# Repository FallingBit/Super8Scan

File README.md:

# Super8Scan

Progetto completo di uno **scanner per pellicole Super8 e Normal8** fatto in casa, a cura di **FallingBit**:
hardware, firmware e software.

Un proiettore modificato fa avanzare la pellicola un fotogramma alla volta; quando l'immagine è ferma simula il click
di un mouse. Un programma per Windows salva a ogni click il fotogramma ripreso da una scheda di acquisizione HDMI/USB
in 4K, controlla la qualità dei fotogrammi e alla fine crea il video MP4.

## Il sistema

Un proiettore Super8/Normal8 **Silma Bivox "D" Lux** modificato è comandato da un **ESP32**. La lampada è sostituita
da un pannello LED a 4000 K e la camera (scheda di acquisizione HDMI/USB 4K) riprende direttamente nell'obiettivo,
senza telo, con tutto il fotogramma e il foro della pellicola. Il cuore del sistema:

- **Motore passo-passo** NEMA 17 con driver TMC2208, collegato alla meccanica originale del proiettore;
- **Sensore Hall** e un magnete sulla ruota dello shutter, per sapere quando il fotogramma è fermo;
- **Optoisolatore** (PC817) collegato al tasto sinistro di un mouse USB: l'ESP32 "fa click" al momento giusto;
- **Display OLED** e led del pannello originale per le informazioni;
- alimentazione a **24 V** (motore), 12 V (illuminazione) e 5 V (logica).

### Funzioni della manopola

Con la manopola originale del proiettore si scelgono le funzioni:

| Posizione della manopola | Funzione |
|---|---|
| **Centro (riposo)** | **STOP**: tutto fermo, lampada spenta |
| Centro, **manopola premuta** | **Caricamento della pellicola**: il motore gira finché la tieni premuta e fa avanzare la pellicola nella meccanica, senza lampada e senza click |
| **1 scatto a destra** | **Lampada accesa**, motore fermo: serve a posizionare la camera davanti all'obiettivo, inquadrare e mettere a fuoco |
| **2 scatti a destra** | **Scansione**: il motore gira, un sensore Hall rileva il fotogramma fermo e l'ESP32 simula il click di un mouse; Super8Scan salva il fotogramma a ogni click |
| **1 scatto a sinistra** | Lampada accesa, motore fermo (preparazione alla marcia indietro) |
| **2 scatti a sinistra** | **Marcia indietro**: il motore gira al contrario, a metà velocità, con la lampada accesa. Serve a tornare indietro di **qualche fotogramma**, per esempio per ripetere la scansione di un tratto |
| **3 scatti a sinistra** | STOP (lampada spenta) |

Non c'è il riavvolgimento veloce: per riavvolgere la bobina si completa la scansione, si fa uscire tutta la pellicola
dal proiettore e la si riavvolge a parte.

Fermando il proiettore si ferma anche l'acquisizione, che può essere ripresa dallo stesso punto anche il giorno dopo.
Prima di cominciare, il puntatore del mouse va posizionato sulla finestra di Super8Scan.

## Esempi di fotogrammi

Quattro fotogrammi di esempio, salvati direttamente dal programma alla massima qualità (4K, JPEG qualità 100), senza
alcuna elaborazione e senza metadati. Cliccando sulla miniatura si apre l'originale (circa 8-9 MB). Si vede l'intero gate,
compreso il foro della pellicola usato dal controllo dei fotogrammi; le immagini sono come le riprende la telecamera
(capovolte: nel video il programma le ribalta con l'opzione apposita).

| | |
|---|---|
|  |  |
|  |  |

**Video di esempio** (Super8, creato da una scansione fatta con questo scanner): <https://youtu.be/SkZqkTiNc5s>

## Contenuto del repository

| Cartella | Contenuto | Stato |
|---|---|---|
| [`software/`](software) | **Super8Scan** per Windows (Python): acquisizione a ogni click, controllo dei fotogrammi, creazione MP4, log delle lavorazioni ([cronologia](software/CHANGELOG.md)) | 1.1.3 |
| [`firmware/`](firmware) | Firmware Arduino per l'ESP32: manopola, motore, lampada, click, display | v2.27 |
| [`hardware/`](hardware) | Descrizione del proiettore modificato, componenti, alimentazione, schema a blocchi; progetto KiCad, gerber del **PCB rev. 2.1** | rev. 2.1 |
| [`docs/`](docs) | Foto del prototipo, immagine del PCB e [fotogrammi di esempio](docs/esempi) | |

## Cosa serve

- **Un proiettore** Super8 (o Normal8) da modificare. Quello usato è un Silma Bivox "D" Lux, ma ogni proiettore con
  meccanica a griffa e shutter a ruota si può adattare. Vedi [`hardware/`](hardware) per l'elenco dei componenti e le
  modifiche.
- **Una scheda di acquisizione** USB con ingresso HDMI (4K UHD) e una camera con uscita HDMI.
- **Un PC con Windows** e Python per il software (vedi sotto).
- Per il firmware: Arduino IDE, una scheda ESP32 (WROOM-32) e le librerie indicate in [`firmware/`](firmware).

## Software Super8Scan

1. Collega la scheda di acquisizione e premi **Apri telecamera** (4K UHD, MJPG o YUY2).
2. Scegli cartella e nome del film, formato (JPG qualità 85–100, oppure PNG senza perdita) e l'attesa dopo il click.
3. **Avvia acquisizione**: ogni click sinistro del mouse, in qualsiasi punto dello schermo, salva un fotogramma
   (`fotogramma_000001.jpg`, ...). Il pulsante *Ferma* non conta. Se la cartella contiene già fotogrammi, la
   numerazione prosegue.
   **Avviso di giuntura**: una bobina da 15 m ha circa 3600 fotogrammi e le bobine più grandi sono bobine piccole
   giuntate dopo lo sviluppo. Intorno a 3600, 7200, 10800… (da 200 fotogrammi prima a 200 dopo, regolabile) la cornice
   dell'anteprima diventa **gialla**, compare un avviso e, se vuoi, suona un segnale: le vecchie giunture possono
   staccarsi o fare uno sbalzo nella meccanica. Le impostazioni sono sotto il pulsante *Avvia acquisizione*; il conteggio
   usa il numero del fotogramma, quindi vale anche se la scansione riprende in una cartella già avviata.
4. **Controllo dei fotogrammi**: il programma misura la posizione del **foro** della pellicola (a sinistra) in tutti i
   fotogrammi. Se è spostato, deformato o sfocato (scia), il fotogramma è sospetto: li vedi in un elenco con le
   miniature e decidi tu quali scartare. Gli scartati non si cancellano: nel video si possono saltare oppure
   sostituire con il fotogramma precedente. Funziona se il foro è ben visibile; con certe pellicole commerciali
   esposte oltre i bordi il foro non si distingue e il controllo non è disponibile.
5. **Crea video MP4**: scegli i fotogrammi/s (Normal8 16, Super8 18, Super8 24 oppure un valore a piacere con *Custom*; il
   programma ricorda l'ultimo usato), il bitrate, il codec (x264 *slow* per la massima qualità, x264 *medium* più veloce, H.265, oppure la scheda
   NVIDIA), la risoluzione, il nome e la cartella di destinazione.
   Due opzioni, attive di default: **ribalta l'immagine in verticale** (lo scanner la riprende capovolta) ed
   **escludi i fotogrammi bianchi in fondo** (la parte finale della scansione, quando la pellicola è finita e
   passa solo la luce). I fotogrammi bianchi non vengono cancellati dalla cartella: sono solo saltati nel video.

**Log della lavorazione**: a ogni *Ferma* il programma scrive nella cartella di lavoro un file di testo
`<film>-<ggmmaaaa>-<hhmm>.txt` (per esempio `1986-17112026-1810.txt`) con il nome del film, la data e l'ora, la
durata della scansione (da *Avvia* a *Ferma*) e il numero di fotogrammi acquisiti. Serve come storico delle lavorazioni.

Lo scatto non prende il fotogramma presente nel momento del click, ma il primo arrivato dopo una breve attesa
(regolabile): le schede di acquisizione tengono qualche immagine in coda.

### Installazione ed esecuzione

Nel repository ci sono **solo i sorgenti**: non vengono pubblicati programmi o firmware già compilati (vedi
[Licenza](#licenza)). Per usare il software lo si esegue o lo si compila dai sorgenti:

```
cd software
python -m venv .venv
.venv\Scripts\python.exe -m pip install -r requirements.txt
.venv\Scripts\python.exe super8scan.py          # con la scheda di acquisizione
.venv\Scripts\python.exe super8scan.py --sim    # telecamera simulata, per provare senza scheda
.venv\Scripts\python.exe tests\test_super8scan.py
.venv\Scripts\python.exe build.py               # crea dist\Super8Scan.exe (per uso personale)
```

Il firmware si compila e si carica con Arduino IDE: vedi [`firmware/README.md`](firmware/README.md) per la scheda, le
impostazioni e le librerie.

### FFmpeg (necessario per creare il video)

FFmpeg **non è incluso**. Scaricalo (per esempio la build *essentials* di <https://www.gyan.dev/ffmpeg/builds/>)
e metti `ffmpeg.exe` nella stessa cartella di `Super8Scan.exe`. In alternativa il programma lo cerca nel `PATH`,
oppure puoi indicarlo con il link «indica…» in fondo al pannello.

## Un esempio di flusso di lavoro

Così lavora l'autore; è solo un'indicazione, ognuno può adattarla.

1. **Preparazione della pellicola**: pulirla e controllare le giunture, rifacendole se serve (l'autore usa una
   giuntatrice a nastro 3M 702, vedi la [foto](docs/README.md#giuntatrice)).
2. **LEAD bianco** (vedi la [foto](docs/README.md#bobine-e-giunzione-del-lead)): se manca, aggiungerlo all'inizio, così non si perde la parte iniziale della pellicola, che serve
   per il caricamento.
3. **Caricamento**: caricare la pellicola fino ai primi fotogrammi e solo allora accendere la lampada. Con pochi led
   il calore è trascurabile e non c'è rischio di bruciare la pellicola.
4. **Fotocamera**: obiettivo macro che permette di riempire il fotogramma e mettere a fuoco; tutto in manuale, niente
   automatismi. Il bilanciamento del bianco si fa **prima** di inserire la pellicola, con la lampada accesa e il suo
   diffusore: così si eliminano le dominanti di colore della luce e il bianco è corretto.
5. **Collegamenti**: avviare Super8Scan, collegare il cavetto USB del proiettore (simulazione del click) e il cavo
   USB 3 della scheda di acquisizione (con successo una Elgato Cam Link 4K, HDMI → USB).
6. **Acquisizione** dei fotogrammi.
7. **Controllo fotogrammi**: analisi e scarto di quelli danneggiati o fuori sincronismo.
8. **Video MP4** in 4K ad alto bitrate.
9. **Postproduzione** (facoltativa) in DaVinci Resolve: correzioni, musica o audio, poi esportazione per la consegna.
10. **Pellicole con pista sonora magnetica**: serve un secondo passaggio con un proiettore sonoro modificato per
    prelevare il segnale direttamente dalle testine audio, l'unico modo per recuperare il sonoro originale. La
    traccia si sistema poi in DaVinci Resolve sotto il video, in sincrono.

## Bobine e durate

Durate standard del film muto (18 fps) e sonoro (24 fps). I fotogrammi sono approssimativi: una bobina da 15 m
(50 piedi) ne ha circa 3600.

| Bobina | Pellicola | Fotogrammi circa | A 18 fps (muto) | A 24 fps (sonoro) |
|---|---|---|---|---|
| 7,5 cm | 15 m (50 piedi) | 3600 | 3 - 3,5 minuti | circa 2,5 minuti |
| 13 cm | 60 m (200 piedi) | 14400 | circa 13 minuti | circa 10 minuti |
| 18 cm | 120 m (400 piedi) | 28800 | 26 - 27 minuti | circa 20 minuti |

In ambito consumer le vecchie cineprese caricavano solo la bobina piccola: le bobine più grandi sono state ottenute
**giuntando** più bobine da 15 m dopo lo sviluppo. Per questo ogni circa 3600 fotogrammi c'è una giuntura, e il software
avvisa (vedi sopra).

## Stato e cose da fare

- Il sistema funziona: scansione, controllo dei fotogrammi e creazione del video sono state provate su pellicole vere.
- Il firmware 2.27 è provato su pellicole vere: scansione a circa 4,8 fotogrammi/s (prima 3,7) e, se il motore si ferma
  su una giuntura, riparte da solo senza perdere né sbagliare fotogrammi. Nelle versioni precedenti (2.25) erano già
  stati risolti il click doppio dopo uno stop, l'errore NO HALL, l'antirimbalzo della manopola e il pulsante del click.
- Limiti del motore misurati: a 6,5 giri/s funziona con margine, a 7,0 regge ma si è fermato su una giuntura, a 7,5 va in
  stallo (vedi [`firmware/README.md`](firmware/README.md)).
- Il controllo dei fotogrammi riconosce anche il foro **Normal8** (provato solo su immagini del LEAD bianco; da provare su pellicola vera) e, in quel caso, preseleziona il formato Normal8 (16 fps) nella sezione *Video MP4*.
- Il sensore Hall usato non è identificato con certezza (vedi [`hardware/README.md`](hardware/README.md)): conta che
  abbia le caratteristiche indicate.

## Avvertenze ed esclusione di responsabilità

Super8Scan è un **progetto hobbistico**, nato per uso personale e condiviso così com'è, senza alcuna garanzia, per chi
fosse interessato a studiarlo o a costruirne uno simile. Non è un prodotto commerciale e non è certificato.

- **Nessuna garanzia sui risultati.** Chi riproduce il progetto, in tutto o in parte (hardware, firmware o software),
  può non ottenere i risultati descritti: dipende dal proiettore, dalla pellicola, dai componenti, dalla scheda di
  acquisizione e dal modo in cui il lavoro viene eseguito. Il progetto è stato provato soltanto sul prototipo
  dell'autore.
- **Rischi elettrici e meccanici.** Il progetto prevede modifiche a un proiettore e l'uso di un alimentatore
  alimentato dalla **tensione di rete (220 V)**, di parti in movimento. Chi lo
  riproduce lo fa **a proprio rischio** e sotto la propria responsabilità, e deve avere le competenze necessarie
  oppure farsi aiutare da una persona competente (vedi anche la sezione «Sicurezza» in
  [`hardware/README.md`](hardware/README.md)).
- **Pellicole e dati.** Le pellicole, soprattutto se vecchie o rare, possono rovinarsi durante il caricamento o la
  scansione; i file prodotti possono contenere errori. Conserva sempre gli originali e controlla i risultati.
- **Esclusione di responsabilità.** L'autore (FallingBit) **declina ogni responsabilità**, nei limiti consentiti dalla
  legge, per danni a persone, cose, apparecchi, pellicole o dati, e per qualunque insuccesso o risultato non
  soddisfacente derivante dalla costruzione o dall'uso di quanto pubblicato in questo repository. Il codice è
  distribuito alle condizioni della licenza MIT, che esclude ogni garanzia (vedi [LICENSE](LICENSE)).

## Licenza

Il codice è libero: puoi copiarlo, modificarlo e distribuirlo, **mantenendo l'avviso di copyright di FallingBit**
(licenza MIT, vedi [LICENSE](LICENSE)). Citare il progetto originale è comunque gradito.

Le librerie di terze parti sono elencate in [THIRD-PARTY-NOTICES.txt](THIRD-PARTY-NOTICES.txt). Alcune hanno licenze
non permissive (per esempio la libreria del firmware MobaTools, LGPL-2.1, e le librerie di OpenCV che includono
FFmpeg con licenza LGPL). Per questo il repository contiene **solo i sorgenti**, senza eseguibili né firmware già
compilati, e il progetto non è destinato alla vendita.

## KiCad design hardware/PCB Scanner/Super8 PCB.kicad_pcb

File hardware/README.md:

# Hardware

Il proiettore usato è un **Silma Bivox "D" Lux** (Super8 e Normal8), ma qualsiasi proiettore con meccanica
a griffa e shutter a ruota si può adattare allo stesso modo.

> **Schema e PCB aggiornati (rev. 2.1)**: i file KiCad e i gerber in [`PCB Scanner/`](PCB%20Scanner) corrispondono
> allo scanner, con alimentazione del motore a 24 V e MS1/MS2 del TMC2208 collegati all'ESP32.

Le foto del prototipo sono in [`../docs/`](../docs/README.md): mostrano la **prima versione** del PCB (serigrafia
«+12v» e fili volanti per MS1/MS2), non la rev. 2.1.

## Componenti principali

Elenco di quanto usato nel prototipo (i componenti sono tutti comuni e facili da trovare).

| Componente | Modello / valore | Note |
|---|---|---|
| Proiettore | Silma Bivox "D" Lux | Super8 e Normal8 |
| Scheda di controllo | **AZDelivery ESP32-WROOM-32** | DevKit C, modulo ESP32-WROOM-32 |
| Driver del motore | **BigTreeTech TMC2208 V3.0** | con dissipatore |
| Motore | NEMA 17 **17HS13-0404S** | 0,4 A per fase; Vref del TMC2208 regolato a circa 0,58 V (≈ 0,4 A) |
| Sensore di posizione | sensore Hall **lineare ratiometrico** a 3 pin, alimentato a 3,3 V; probabilmente Allegro **A1304** (da confermare: marcature `555G` e `1150`). Va bene qualsiasi sensore con le stesse caratteristiche (vedi sotto) | con magnete sulla ruota dello shutter |
| Optoisolatore | **PC817**, led interno con resistenza da **1 kΩ** | pilotato dal pin 18 dell'ESP32 (3,3 V); simula il click del tasto sinistro del mouse |
| Relé | modulo relé a 1 canale, 5 V, con led di stato (tipo JQC-3F-05VDC-C, 10 A) | accende e spegne il pannello LED (contatti a 12 V) |
| Convertitori DC/DC | 2 moduli step-down **LM2596** regolabili | uno regolato a 12 V, uno a 5 V |
| Display | modulo OLED 0,91", 128×32, **SSD1306**, I2C (0x3C) | |
| Led di tensione sul PCB | 1 rosso (24 V) con resistenza da 1,8 kΩ; 1 verde (5 V) con resistenza da 330 Ω | |
| Led del pannello frontale | 3 led comuni: rosso, verde, blu, con resistenze da 330 Ω | quelli del pannello originale Silma |
| Condensatori | 100 µF 50 V elettrolitico sui 24 V; 100 nF ceramico sui 5 V | filtro dell'alimentazione |
| Illuminazione | striscia LED a 12 V, 4000 K, tagliata in quattro pezzi corti affiancati | con diffusore di opalina (o plexiglass opaco) |
| Alimentatore | switching 220 V → 24 V | |

## Schema a blocchi

```mermaid
flowchart LR
    RETE["Rete 220 V"] --> ALI["Alimentatore switching<br/>220 V → 24 V"]
    ALI -->|24 V| TMC["Driver TMC2208"]
    TMC --> MOT["Motore passo-passo<br/>NEMA 17<br/>(meccanica originale)"]
    ALI -->|24 V| DC12["DC/DC step-down<br/>24 → 12 V"]
    DC12 -->|12 V| REL["Relé"]
    REL --> LED["Pannello LED 4000 K"]
    DC12 -->|12 V| DC5["DC/DC step-down<br/>12 → 5 V"]
    DC5 -->|5 V logica| ESP["ESP32-WROOM-32"]
    ESP -->|STEP/DIR/EN/MS1/MS2| TMC
    ESP -->|comando| REL
    ESP -->|3,3 V| HALL["Sensore Hall"]
    HALL -->|analogico| ESP
    ESP --> OPTO["Optoisolatore"] --> MOUSE["Tasto sinistro<br/>di un mouse USB"] --> PC["PC con Super8Scan"]
    MAN["Manopola originale<br/>+ pulsante click"] --> ESP
    ESP --> OLED["Display OLED + led Silma"]
```

## Alimentazione

| Tratto | Tensione | Note |
|---|---|---|
| Alimentatore switching | 220 V → **24 V** | unico collegamento alla rete |
| Motore (pin VM del TMC2208) | 24 V | |
| DC/DC step-down n. 1 | 24 → 12 V | alimenta il pannello LED, passando dal relé, e il secondo convertitore |
| DC/DC step-down n. 2 | 12 → 5 V | logica (ESP32) |
| ESP32 (scheda di controllo) | 5 V | pin 5 V / VIN della scheda |
| Modulo relé | 5 V | ingresso pilotato dal pin 23 dell'ESP32 (3,3 V) |
| Display OLED | 5 V | collegato all'I2C dell'ESP32 |
| Sensore Hall | 3,3 V | dal regolatore di bordo dell'ESP32 |

Il relé, pilotato dall'ESP32, funziona da interruttore dei 12 V del pannello LED.

Nota sul display: nel prototipo il modulo OLED è alimentato a 5 V e SDA/SCL, misurati verso massa, restano a 3,3 V
(il modulo ha le pull-up sul lato a 3,3 V). Con un altro modulo, prima di collegarlo a 5 V, misura SDA e SCL:
se leggi circa 5 V alimentalo a 3,3 V, perché i pin dell'ESP32 non tollerano i 5 V.

## Modifiche al proiettore

- **Lampada**: tolta la lampada alogena dicroica. Al suo posto un mini-pannello a LED autocostruito a **4000 K**
  (luce neutra): una striscia LED a 12 V tagliata in quattro pezzi più corti, affiancati su una basetta
  millefori, con davanti un diffusore di opalina (o plexiglass opaco) che elimina il tipico punto luminoso al centro
  della proiezione. I led sono distanziati e c'è molta aria intorno: il pannello **non scalda** (vedi le foto in
  [`docs/`](../docs/README.md#pannello-led)).
  Il pannello è alimentato dal convertitore a 12 V tramite il relé.
- **Gate (finestra)**: modificato per la massima apertura, così si riprende **tutto il fotogramma senza crop**;
  nell'immagine si vede anche il foro della pellicola.
- **Motore**: stepper NEMA 17 con driver **TMC2208**; fa girare la meccanica originale (caricamento e avanzamento).
  Nel primo PCB i piedini **MS1 e MS2** del driver erano fissati con un ponticello fatto con le piste, quindi il
  passo non si poteva cambiare. Nel prototipo sono stati scollegati e collegati con due **fili volanti** ai pin
  **13 (MS1) e 15 (MS2)** dell'ESP32, così il firmware sceglie i microstep (ora 1/2 di passo) e si ottiene una
  velocità del motore maggiore. Nel PCB rev. 2.1 queste due connessioni sono già sulle piste.
- **Sensore di posizione**: magnete incollato sulla ruota dello shutter, in corrispondenza del "fotogramma pronto",
  letto da un sensore Hall a 3 pin montato in un supporto stampato in 3D. Il modello esatto non è certo: probabilmente
  un Allegro **A1304** (sensore lineare per 3,3 V), ma le marcature sul componente (`555G` e `1150`) non lo confermano.
  Quello che conta sono le sue caratteristiche, misurate con il tester sul prototipo:
  - sensore **lineare ratiometrico** alimentato a 3,3 V (dal regolatore dell'ESP32);
  - uscita a riposo, lontano dal magnete: **1,6 V** (circa metà dell'alimentazione);
  - uscita vicino al magnete: **1,2 V** (la tensione scende al passaggio del magnete).

  Un sensore equivalente con queste caratteristiche funziona. Il firmware legge l'uscita con l'ingresso analogico
  dell'ESP32 e due soglie (vedi il README del firmware): con un altro sensore o un altro magnete le soglie vanno
  ritarate.
- **Click del mouse**: un piccolo mouse USB smontato, alimentato dal **suo cavo USB direttamente dal PC** e visto
  dal PC come un normale mouse. Due fili sono saldati in parallelo al contatto del **tasto sinistro**:
  vanno ai pin del **PC817** lato transistor, **pin 4 (collettore) sul segnale** del tasto e **pin 3 (emettitore)
  sulla massa del mouse**. Il led interno (pin 1 e 2) è pilotato dall'ESP32 tramite la resistenza da 1 kΩ
  (pin 1 verso l'ESP32, pin 2 a massa).
  Quando l'ESP32 accende il led, il transistor chiude il contatto come un dito sul tasto. Il PC817 isola
  elettricamente il proiettore dal PC: i due circuiti non hanno nessun collegamento in comune.
  Il puntatore va posizionato sulla finestra di Super8Scan prima di iniziare.
- **Manopola e led**: usati la manopola e il pannello originali Silma (3 led di segnalazione), più un piccolo
  display OLED 128×32.
- **Normal8**: il proiettore ha un comando per passare tra Super8 e Normal8. Il formato del foro della pellicola
  cambia e andrà gestito nel controllo dei fotogrammi del software (da fare).

## PCB (rev. 2.1)

Cartella [`PCB Scanner/`](PCB%20Scanner): progetto KiCad (`Super8 PCB.kicad_pro`, `.kicad_sch`, `.kicad_pcb`) e
file di produzione (`S8Gerber/` e `S8Gerber.zip`). Immagine del circuito (fronte e retro):
[`docs/foto/PCB.webp`](../docs/foto/PCB.webp). La scheda ESP32 e il modulo TMC2208 si infilano sul PCB; il resto sono
connettori a pin.

| Connettore / parte | Collegamento | Pin ESP32 |
|---|---|---|
| POWER | +24 V, +5 V, GND | alimenta il motore (24 V), la logica e l'ESP32 (5 V) |
| STEPPER | 4 fili del motore | via TMC2208 |
| TMC2208 | DIR, STEP, EN | 33, 25, 26 |
| TMC2208 | MS1, MS2 (microstep) | 13, 15 |
| HALL | segnale (S), GND, +3,3 V | 34 (nessuna resistenza di pull-up sul PCB) |
| SWITCH | 5 contatti della manopola | 5, 17, 16, 4, 2 |
| LED | GND + 3 led (MOTOR, LAMP, GRAB) con resistenza da 330 Ω | 27, 14, 12 |
| Rele Lamp | +5 V, GND, comando | 23 |
| Mouse click (J7) | pin 3 e 4 del PC817 (lato transistor) | led del PC817 da pin 18, con resistenza da 1 kΩ |
| pulsante (J9) | pulsante che abilita/disabilita il click, tra il pin 2 e la massa | 19 (pull-up interna dell'ESP32) |
| OLED | GND, +5 V, SCL, SDA | 22 (SCL), 21 (SDA) |
| LED 24 V / LED 5 V | led rosso con 1,8 kΩ / verde con 330 Ω | |
| C1 / C2 | 100 µF sui 24 V / 100 nF sui 5 V | |

## Sicurezza

Questo è un progetto hobbistico: chi lo riproduce lo fa a proprio rischio e l'autore declina ogni
responsabilità (vedi le [avvertenze nel README principale](../README.md#avvertenze-ed-esclusione-di-responsabilità)).

- L'alimentatore lavora a **tensione di rete (220 V)**: monta l'alimentatore in un contenitore chiuso, con fusibile
  e senza parti sotto tensione accessibili. Se non hai esperienza con la rete elettrica, usa un alimentatore
  esterno già certificato (adattatore 24 V).
- Nel prototipo **non c'è nessun fusibile**. Chi costruisce il proprio scanner farebbe bene a metterne uno sulla
  linea a 24 V, dopo l'alimentatore.
- Il motore a 24 V e le parti in movimento del proiettore: spegni sempre prima di mettere le mani nel meccanismo.
- I due convertitori **LM2596** sono regolabili: **regola e misura con il tester le tensioni di uscita (12 V e 5 V)
  prima di collegare ESP32, relé e display**. Una tensione sbagliata sulla logica a 5 V può danneggiarli.
- **STACCA L'ALIMENTAZIONE DEL PROIETTORE PRIMA DI COLLEGARE L'ESP32 ALLA USB DEL PC.** Per programmare l'ESP32 con
  il cavo USB l'alimentatore del proiettore va scollegato. La scheda dell'autore ha un diodo che impedisce il ritorno
  di corrente tra le due alimentazioni, ma altre schede potrebbero non averlo: alimentarle insieme dal convertitore e
  dalla porta USB può danneggiare la scheda o la porta del PC.
- A valle dell'alimentatore le tensioni sono basse (24 V), ma un cortocircuito può comunque scaldare e danneggiare
  cavi e componenti: controlla i collegamenti prima di dare tensione.

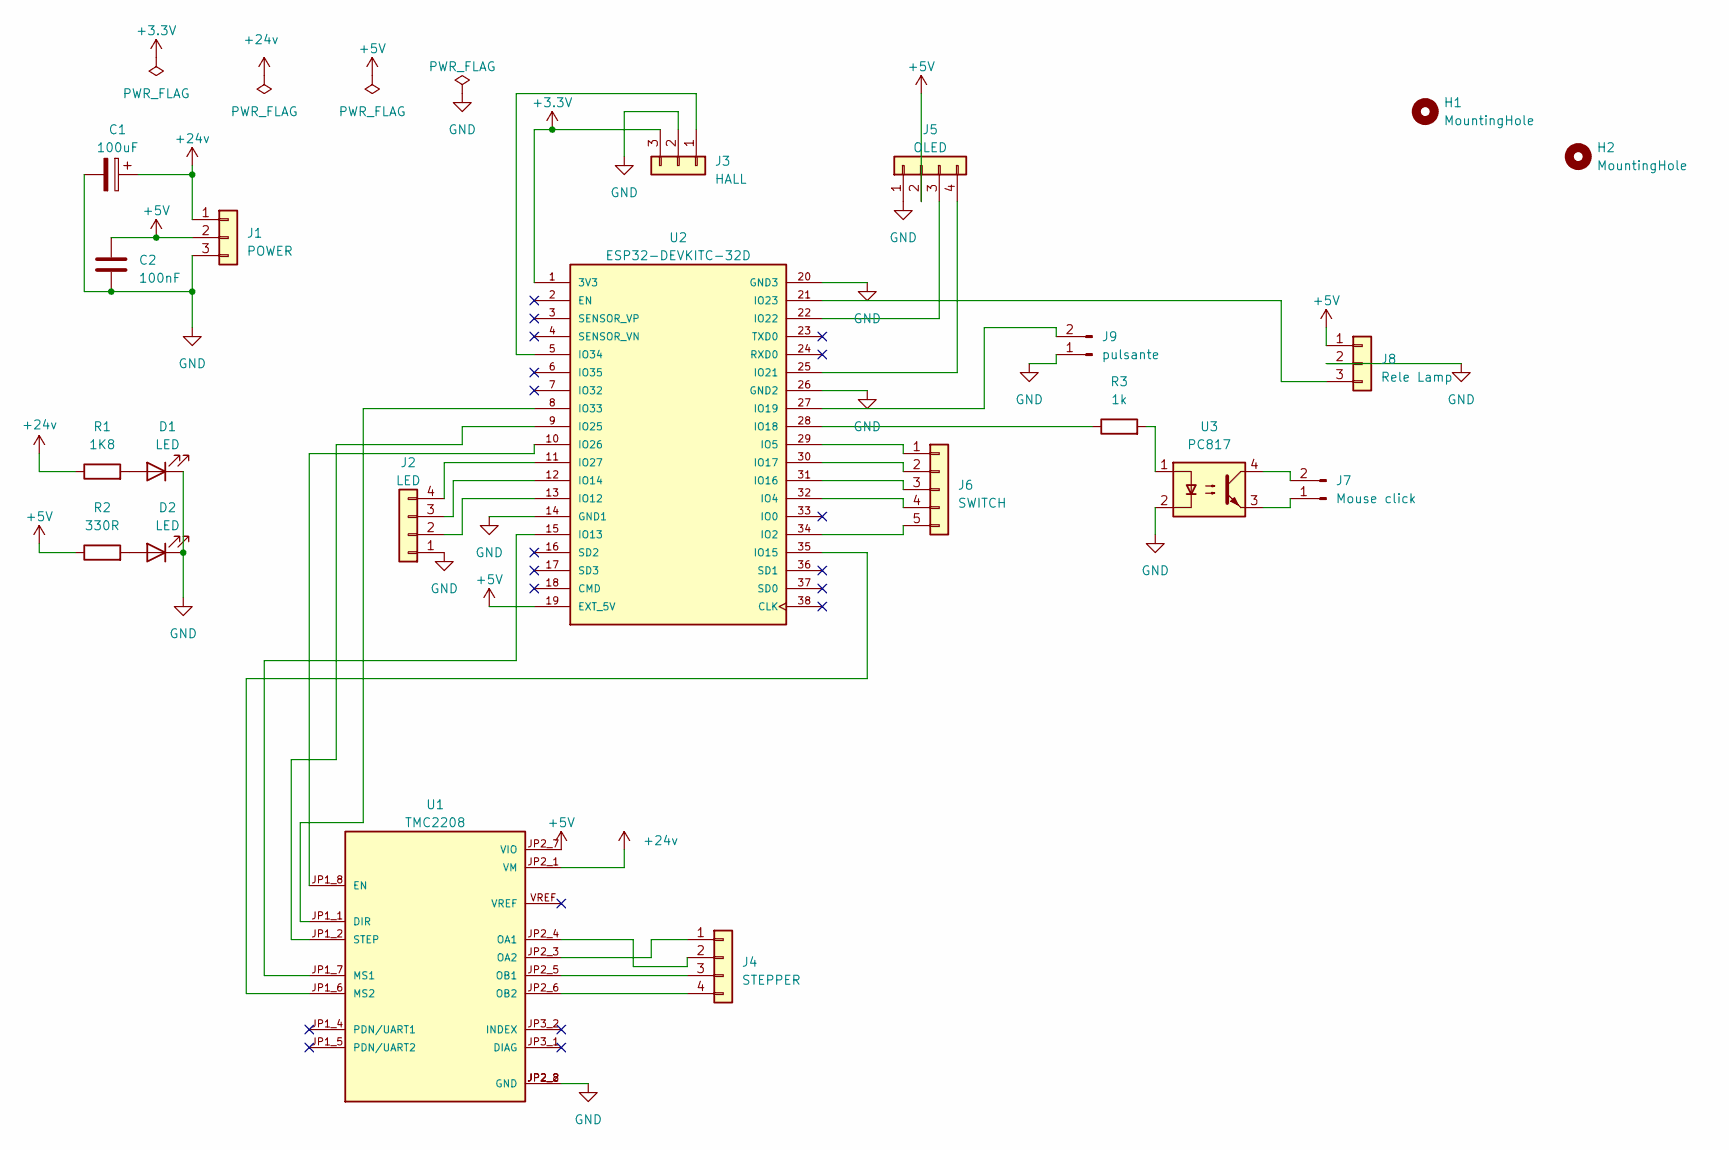
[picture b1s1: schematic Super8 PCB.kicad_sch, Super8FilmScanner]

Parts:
C1: 100uF; CP_Radial_D6.3mm_P2.50mm
C2: 100nF; C_Rect_L7.0mm_W2.5mm_P5.00mm
D1, D2: LED; LED_D3.0mm_Clear
H1, H2: MountingHole; MountingHole_4.3mm_M4_Pad_Via
J1: POWER; PinSocket_1x03_P2.54mm_Vertical
J2: LED; PinSocket_1x04_P2.54mm_Vertical
J3: HALL; PinSocket_1x03_P2.54mm_Vertical
J4: STEPPER; PinSocket_1x04_P2.54mm_Vertical
J5: OLED; PinSocket_1x04_P2.54mm_Vertical
J6: SWITCH; PinSocket_1x05_P2.54mm_Vertical
J7: Mouse click; PinSocket_1x02_P2.54mm_Vertical
J8: Rele Lamp; PinSocket_1x03_P2.54mm_Vertical
J9: pulsante; PinSocket_1x02_P2.54mm_Vertical
R1: 1K8; R_Axial_DIN0309_L9.0mm_D3.2mm_P12.70mm_Horizontal
R2: 330R; R_Axial_DIN0309_L9.0mm_D3.2mm_P12.70mm_Horizontal
R3: 1k; R_Axial_DIN0309_L9.0mm_D3.2mm_P12.70mm_Horizontal
U1: TMC2208; MODULE_TMC2208_SILENTSTEPSTICK
U2: ESP32-DEVKITC-32D; MODULE_ESP32-DEVKITC-32D; PARTREV 4
U3: PC817; DIP-4_W7.62mm

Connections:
+3.3V: J3.3, U2.1 (3V3)
+5V: C2.1, J1.2, J5.2, J8.1, R2.1, U1.JP2_7 (VIO), U2.19 (EXT_5V)
+24v: C1.1, J1.1, R1.1, U1.JP2_1 (VM)
GND: C1.2, C2.2, D1.1 (K), D2.1 (K), J1.3, J2.1, J3.2, J5.1, J8.2, J9.1, U1.JP2_2 (GND), U1.JP2_8 (GND), U2.14 (GND1), U2.20 (GND3), U2.26 (GND2), U3.2
unnamed: D1.2 (A), R1.2
unnamed: D2.2 (A), R2.2
unnamed: J2.2, U2.13 (IO12)
unnamed: J2.3, U2.12 (IO14)
unnamed: J2.4, U2.11 (IO27)
unnamed: J3.1, U2.5 (IO34)
unnamed: J4.1, U1.JP2_3 (OA2)
unnamed: J4.2, U1.JP2_4 (OA1)
unnamed: J4.3, U1.JP2_5 (OB1)
unnamed: J4.4, U1.JP2_6 (OB2)
unnamed: J5.3, U2.22 (IO22)
unnamed: J5.4, U2.25 (IO21)
unnamed: J6.1, U2.29 (IO5)
unnamed: J6.2, U2.30 (IO17)
unnamed: J6.3, U2.31 (IO16)
unnamed: J6.4, U2.32 (IO4)
unnamed: J6.5, U2.34 (IO2)
unnamed: J7.1, U3.3
unnamed: J7.2, U3.4
unnamed: J8.3, U2.21 (IO23)
unnamed: J9.2, U2.27 (IO19)
unnamed: R3.2, U3.1
unnamed: U1.JP1_1 (DIR), U2.8 (IO33)
unnamed: U1.JP1_8 (EN), U2.10 (IO26)
unnamed: U1.JP1_7 (MS1), U2.15 (IO13)
unnamed: U1.JP1_6 (MS2), U2.35 (IO15)
unnamed: U1.JP1_2 (STEP), U2.9 (IO25)
unnamed: R3.1, U2.28 (IO18)

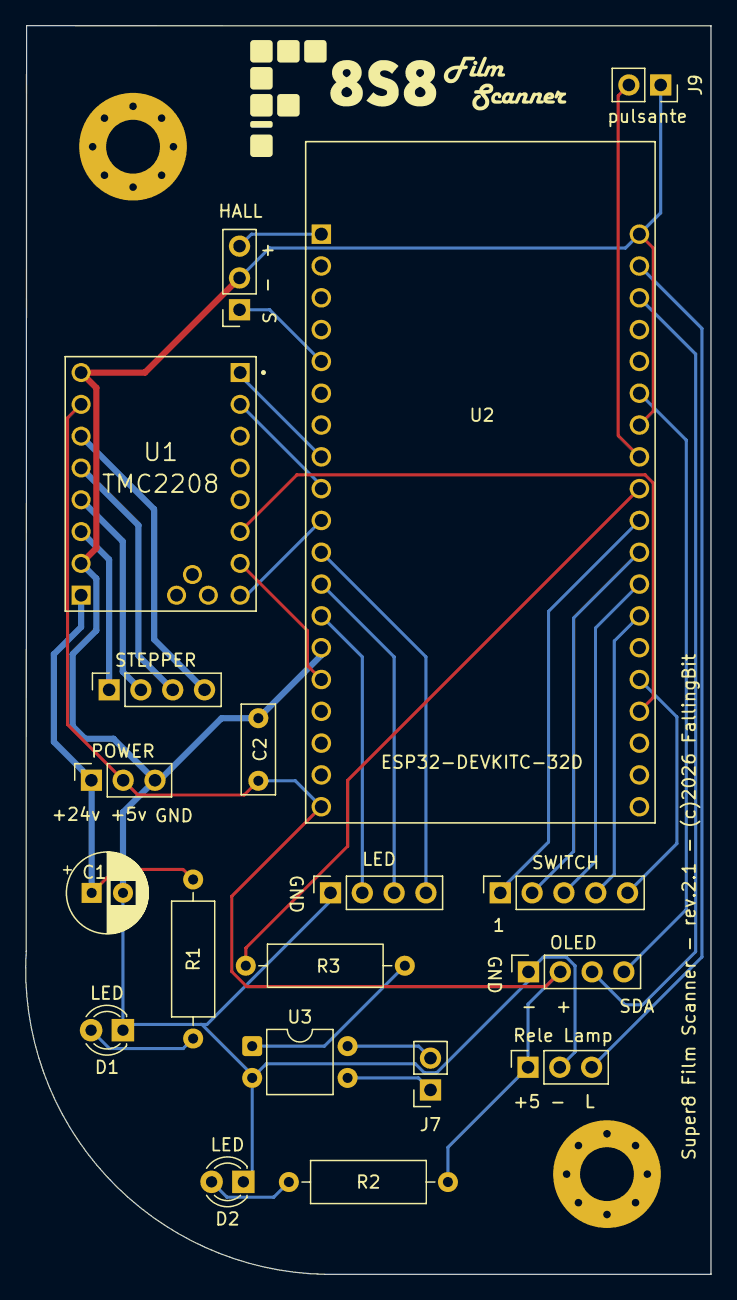
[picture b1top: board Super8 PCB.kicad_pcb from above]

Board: 2 copper layers, 54.7 x 99.7 mm, 21 parts (0 on the bottom side), 32 nets.

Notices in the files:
hardware/PCB Scanner/Super8 PCB.kicad_pcb:
Super8 Film Scanner - rev.2.1 - (c)2026 FallingBit
